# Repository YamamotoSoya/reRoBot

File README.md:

# reRoBot
Autonomous navigation robot for the Tsukuba Challenge

## Documentation
- **[docs/TODO.md](docs/TODO.md)** — 今取り組むこと (ジャンル別)
- **[docs/README.md](docs/README.md)** — docs/ 全体の地図 (調査記録・設計文書・解説書・月別変更履歴の索引)
- **[運用手引き (詳細版 README)](docs/manual/00_index.md)** — 全体像・セットアップ・基本パラメータ・起動と手動操作・bag 記録・SLAM (slam_toolbox / GLIM / LIO-SAM)・2D 地図変換・Nav2 / amcl・つくチャレ当日手順・トラブルシューティング・[ソフトウェア構成図](docs/manual/16_software_architecture.md)
- [CLAUDE.md](CLAUDE.md) — 開発規約・ビルド規則・アーキテクチャ要約
- [docs/text/](docs/text/README.md) — テーマ別解説書
- [docs/monthly/](docs/monthly/00_index.md) — 月別の変更履歴 (何を・なぜ変えたか、2026-03〜)

## Setup
### clone
Please add '--recursive' option when you clone this repository
```bash
$ git clone --recursive https://github.com/YamamotoSoya/reRoBot.git
```

If submodules are missing (cloned without `--recursive`):
```bash
$ git submodule update --init --recursive
```
### docker
```bash
$ xhost +local:docker          # set host before activate docker
$ ./scripts/build.sh images    # build images one by one (never `docker compose build` with no args)
$ docker compose up -d main    # activate (main only; other profiles when needed)
$ docker exec -it rerobot_env bash # enter
$ docker compose down          # deactivate
```
### colcon build
```bash
$ cd /workspace
$ rosdep update
$ rosdep install --from-paths src --ignore-src --simulate # check dependencies

$ colcon build --symlink-install --executor sequential
$ source install/setup.bash
```
### Hardware setup
* **USB-CAN アダプタ (CANUSB) — can0 は挿すだけで自動起動**

セットアップ済みのマシンでは、USB-CAN アダプタ (FTDI FT232, `0403:6001`) を挿すと
udev ルール → `/dev/ttyCANUSB` 作成 → systemd サービス `canusb-up.service` → `slcand` (1 Mbps) + `can0` up
まで全自動で行われる。**手動操作は不要**。状態確認・復旧は `./scripts/can_up.sh`。

```bash
$ ip link show can0        # 動作確認 (UP になっていれば OK)
$ ./scripts/can_up.sh      # 落ちているときの確認 + 復旧
```

<details>
<summary><b>新しいマシンをセットアップする手順 (初回のみ)</b></summary>

1. can-utils のインストール
```bash
$ sudo apt-get update && sudo apt-get install can-utils
```

2. カーネルモジュールの自動ロード設定 — `/etc/modules-load.d/can.conf` に以下を記述
```
can
can_raw
slcan
```

3. udev ルール — `/etc/udev/rules.d/99-hokuyo-devices.rules` (新規なら任意の `.rules` ファイル) に追記。
アダプタに固定名 `/dev/ttyCANUSB` を与え、挿入時に systemd サービスを起動させる
```
# CANUSB
SUBSYSTEM=="tty", ATTRS{idVendor}=="0403", ATTRS{idProduct}=="6001", SYMLINK+="ttyCANUSB", MODE="0666", TAG+="systemd", ENV{SYSTEMD_WANTS}="canusb-up.service"
```

4. systemd サービス — `/etc/systemd/system/canusb-up.service` を作成
```ini
[Unit]
Description=Setup CANUSB interface (can0)
After=dev-ttyCANUSB.device
BindsTo=dev-ttyCANUSB.device

[Service]
Type=oneshot
RemainAfterExit=yes
# 2026-09-19: USB 再列挙直後に自動起動した slcand が「can0 UP・送信可・受信ゼロ」の半死状態を
# 作ることがある (同日 3 回: 15:35, 17:16, 17:59。手動 restart で毎回復帰)。sleep 2 を入れても
# 17:59 に再発したので、待ち時間ではなく「起動後に受信を確認し、無ければ slcand をやり直す」で対処する。
ExecStartPre=/bin/sleep 2
ExecStart=/bin/bash -c 'slcand -o -c -s8 /dev/ttyCANUSB can0 && ip link set can0 up'
# EPOS のロジック電源が入っていれば heartbeat (2 ノード × 0.5 Hz) が 4 s 以内に届く。届かなければ 1 回やり直す。
ExecStartPost=/bin/bash -c 'sleep 4; [ "$(cat /sys/class/net/can0/statistics/rx_packets)" -gt 0 ] || { killall slcand; sleep 1; slcand -o -c -s8 /dev/ttyCANUSB can0 && ip link set can0 up; }'
ExecStop=/bin/bash -c 'ip link set can0 down; killall slcand'

[Install]
WantedBy=dev-ttyCANUSB.device
```

既にセットアップ済みのマシンで行を足すときは、上のファイルを編集してから
`sudo systemctl daemon-reload` (アダプタの挿し直しで反映)。半死状態の検知と復旧は
`./scripts/can_up.sh` でも行える (3 s 間 送信ありで受信ゼロなら service を再起動する)。
⚠️ 再列挙のたびに can0 は作り直され、稼働中の ros2_canopen master は旧 can0 を掴んだままになる
(`epos4_controller` が「can0 が作り直された … 再 launch が必要」を ERROR で出す) → `scripts/stop.sh` → 再 launch。

5. 有効化と動作確認
```bash
$ sudo systemctl daemon-reload
$ sudo systemctl enable canusb-up.service
$ sudo udevadm control --reload
# アダプタを挿し直して:
$ ip link show can0
```

※ `slcand -s8` が 1 Mbps 指定。can0 は slcan インターフェースなので、ビットレートを
`ip link set ... type can bitrate ...` で変更することはできない (slcand 側で決まる)。
</details>

* **3D LiDAR (R-Fans-16, Ethernet) — 挿すだけで自動接続**

セットアップ済みのマシンでは、LiDAR 用 USB-Ethernet アダプタ (`enx6c1ff7be7a78`) を挿すと
NetworkManager プロファイル `rfans` が自動適用され、ホストに静的 IP `192.168.0.100/24` が付く。
LiDAR 実機は `192.168.0.3` で、データは UDP 2014 へブロードキャストされる (ホスト側 IP を LiDAR に教える必要はない)。
コンテナは `network_mode: host` なので、ホストに IP が付けば追加設定なしで届く。

```bash
$ ip -br addr show enx6c1ff7be7a78   # 192.168.0.100/24 が付いていれば OK
$ ping -c 3 192.168.0.3              # LiDAR 疎通確認
```

<details>
<summary><b>新しいマシン / 別のアダプタをセットアップする手順 (初回のみ)</b></summary>

NetworkManager に「このアダプタが現れたら固定 IP を付ける」プロファイルを 1 度作るだけ。
`ip addr add` と違い再起動・抜き差しをまたいで自動適用される。

1. LiDAR 用アダプタを挿し、インターフェース名を確認 (`enx` + アダプタの MAC。個体固有で、
   どの USB ポート/ハブ経由でも同じ名前になる)

```bash
$ ip -br link      # 例: enxcce1d5021885
```

2. プロファイル作成 (`ifname` は上で確認した名前に差し替える)

```bash
$ nmcli connection add type ethernet \
    con-name rfans \
    ifname enxcce1d5021885 \
    ipv4.method manual \
    ipv4.addresses 192.168.0.100/24 \
    connection.autoconnect yes \
    connection.autoconnect-priority 100
$ nmcli connection up rfans   # 初回のみ即時有効化 (以後は挿すだけで自動)
```

3. 疎通確認

```bash
$ ip -br addr show <ifname>   # 192.168.0.100/24 が付いていること
$ ping -c 3 192.168.0.3
```

※ gateway を指定していないのでデフォルトルートは奪わず、Wi-Fi のインターネット接続と共存できる。
※ `ifname` 紐付けは MAC 由来名なので「この個体 = LiDAR 係」の専用化が前提。アダプタを
別個体に交換したら手順 1〜2 をやり直す (`nmcli con delete rfans` で旧設定を消してから)。
※ `autoconnect-priority 100` は、ifname 指定なしの汎用「Wired connection」系プロファイルとの
競合時に rfans を勝たせるための指定。
</details>

* **2D LiDAR (HOKUYO UTM-30LX) — 挿すだけで固定名 `/dev/ttyUSB-utm-30lx`**

udev ルールにより、挿すと固定名 `/dev/ttyUSB-utm-30lx` (権限 0666) が作られる。
この名前は `rerobot_bringup_2d.launch.py` の `serial_port` デフォルト値と一致しているので、
**挿すだけで 2D bringup がそのまま動く** (systemd サービス等は不要 — シリアル直結なので
名前と権限さえ固定できればよい)。

```bash
$ ls -l /dev/ttyUSB-utm-30lx    # symlink が ttyUSB* を指していれば OK
```

<details>
<summary><b>新しいマシンをセットアップする手順 (初回のみ)</b></summary>

CANUSB と同じ `/etc/udev/rules.d/99-hokuyo-devices.rules` に追記:

```
# UTM-30LX
SUBSYSTEM=="tty", ATTRS{idVendor}=="15d1", ATTRS{idProduct}=="0000", SYMLINK+="ttyUSB-utm-30lx", MODE="0666"
```

```bash
$ sudo udevadm control --reload
# 挿し直して:
$ ls -l /dev/ttyUSB-utm-30lx
```

※ `MODE="0666"` は「dialout グループに入っていなくても読み書きできる」ようにするため。
これが無いと urg_node が Permission denied で落ちる。
</details>

* **IMU (BNO086 ボード) — 挿すだけで固定名 `/dev/bno086`**

udev ルールにより、通常動作 (firmware 書き込み済み) のボードを挿すと固定名 `/dev/bno086`
(権限 0666) が作られる。番号が変動する `/dev/ttyACM*` を追いかける必要はない。
`bno086_imu_driver` の `port` パラメータ既定値は `/dev/ttyACM0` なので、起動時は
`port:=/dev/bno086` を指定する。

```bash
$ ls -l /dev/bno086             # symlink が ttyACM* を指していれば OK
```

<details>
<summary><b>新しいマシンをセットアップする手順 (初回のみ)</b></summary>

ルールはドライバ同梱の `ros2_ws_main/src/drivers/BNO086_ROS2Board-main/tools/99-bno086.rules`
と同内容。`/etc/udev/rules.d/99-hokuyo-devices.rules` に追記でも、同梱ファイルの
`sudo cp` でもよい:

```
# bno086
# Running firmware: USB CDC. Note that 0483:5740 is ST's generic CDC pair, so
# any other STM32 CDC device would match too - drop the SYMLINK line if you
# have more than one plugged in at once.
SUBSYSTEM=="tty", ATTRS{idVendor}=="0483", ATTRS{idProduct}=="5740", MODE="0666", SYMLINK+="bno086"

# ROM bootloader (S2 BOOT + S1 RESET), so STM32_Programmer_CLI / dfu-util can
# flash without sudo.
SUBSYSTEM=="usb", ATTRS{idVendor}=="0483", ATTRS{idProduct}=="df11", MODE="0666"

# ST-Link, for SWD flashing via OpenOCD / st-flash.
SUBSYSTEM=="usb", ATTRS{idVendor}=="0483", ATTRS{idProduct}=="374b", MODE="0666"
SUBSYSTEM=="usb", ATTRS{idVendor}=="0483", ATTRS{idProduct}=="3748", MODE="0666"
```

```bash
$ sudo udevadm control --reload
# 挿し直して:
$ ls -l /dev/bno086
```

3 ブロックの役割:

| ブロック | ボードの状態 | 用途 |
|----------|--------------|------|
| `0483:5740` (CDC) | 通常動作 (firmware 実行中) | IMU データ読み取り。`/dev/bno086` を作る |
| `0483:df11` (DFU) | ROM ブートローダ (S2 BOOT + S1 RESET で起動) | `STM32_Programmer_CLI` / `dfu-util` での firmware 書き込みを sudo なしで |
| `0483:374b` / `3748` (ST-Link) | — (書き込み器側) | OpenOCD / st-flash での SWD 書き込みを sudo なしで |

※ `0483:5740` は ST 汎用の CDC ID なので、**別の STM32 CDC デバイスを同時に挿すと
そちらにも `/dev/bno086` が付き得る**。複数挿す運用になったら SYMLINK 行を外すか
シリアル番号 (`ATTRS{serial}`) で絞る。
</details>

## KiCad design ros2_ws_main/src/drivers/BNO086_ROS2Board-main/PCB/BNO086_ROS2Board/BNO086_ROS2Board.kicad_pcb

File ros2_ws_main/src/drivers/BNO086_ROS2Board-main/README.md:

# BNO086_ROS2Board

BNO086 (9軸IMU) + STM32F042 の自作基板を、ROS 2 の IMU センサとして使うための
一式です。回路図・基板データからファームウェア、ROS 2 パッケージまで全部入りです。

```
┌──────────────┐   SPI    ┌──────────────┐   USB CDC / UART   ┌─────────────┐
│   BNO086     ├─────────►│  STM32F042C6 ├───────────────────►│   ROS 2     │
│  (SH-2/SHTP) │          │  (firmware/) │   独自バイナリ      │  (ros2_ws/) │
└──────────────┘          └──────────────┘                    └─────────────┘
                                                    sensor_msgs/Imu
                                                    sensor_msgs/MagneticField
```

| ディレクトリ | 内容 |
|---|---|
| `PCB/` | KiCad の回路図・基板データ (既存) |
| `firmware/` | STM32F042C6 用ファームウェア (CMake + STM32 HAL) |
| `ros2_ws/` | ROS 2 ワークスペース (`bno086_imu_driver` パッケージ) |
| `tools/` | udev ルール、シリアル↔TCP 中継 |
| `docker/` | ROS 2 コンテナ (macOS 用。[付録](#付録-macos-で動かす)) |
| `docs/` | [ハードウェア仕様](docs/HARDWARE.md) / [プロトコル仕様](docs/PROTOCOL.md) |

## 動作環境

**Ubuntu 24.04 + ROS 2 Jazzy をネイティブに入れた PC** を前提にしています。
基板は USB CDC で `/dev/ttyACM*` として見えるので、追加のハードウェアは要りません。

| | 用途 | 備考 |
|---|---|---|
| **ROS 2 Jazzy** | ドライバの実行 | 他のディストリでも動くはずですが未検証 |
| **python3-serial** | シリアル通信 | `rosdep` で入ります |
| **ARM ツールチェーン** | ファームウェアのビルド | 書き込み済みの基板を使うだけなら不要 |
| **書き込み手段** | 基板への書き込み | USB だけで済む DFU、または ST-Link |

macOS でも動きますが、Docker Desktop が USB を渡せないため中継が要ります。
開発中の検証用なので[付録](#付録-macos-で動かす)にまわしました。

## クイックスタート

書き込み済みの基板と ROS 2 Jazzy が手元にある場合。

```bash
git clone https://github.com/MechanicalGirlDev/BNO086_ROS2Board.git
cd BNO086_ROS2Board

# シリアルポートの権限 (これを忘れると Permission denied になります)
sudo cp tools/99-bno086.rules /etc/udev/rules.d/
sudo udevadm control --reload-rules && sudo udevadm trigger

source /opt/ros/jazzy/setup.bash
cd ros2_ws
rosdep install --from-paths src --ignore-src -r -y
colcon build --symlink-install && source install/setup.bash

ros2 launch bno086_imu_driver bno086.launch.py port:=/dev/bno086
```

`ros2 topic hz /imu/data` で 100 Hz 出ていれば成功です。
ROS 2 をまだ入れていない場合は [3. PC 側 ROS 2 環境](#3-pc-側-ros-2-環境) から。

| 手順 | 節 |
|---|---|
| ファームウェアをビルドする | [1](#1-ファームウェアのビルド) |
| 基板に書き込む | [2](#2-書き込み) |
| ROS 2 とこのパッケージを入れる | [3](#3-pc-側-ros-2-環境) |
| ノードを起動してトピックを見る | [4](#4-実行) |
| 座標系と実装角度を理解する | [座標系](#座標系) |
| キャリブレーションする | [5](#5-キャリブレーション) |
| うまくいかないとき | [トラブルシューティング](#トラブルシューティング) |
| 既知の問題を確認する | [実機での検証状況](#実機での検証状況) |
| macOS で動かす (検証用) | [付録](#付録-macos-で動かす) |

## 設計方針

**micro-ROS は使っていません。** STM32F042C6 は RAM 6 KiB / Flash 32 KiB しかなく、
micro-ROS (最低でも RAM 30 KiB 程度) は載りません。代わりに軽量な独自バイナリ
プロトコルで PC に送り、PC 側の ROS 2 ノードが `sensor_msgs/Imu` に変換します。

同じ理由で、CEVA 公式の `sh2` ライブラリではなく、必要な部分だけを実装した
軽量 SHTP/SH-2 クライアント (`firmware/App/bno08x.c`) を使っています。
MCU 側は浮動小数点演算を一切行わず、BNO086 の固定小数点値をそのまま転送します。

現在の使用量: **Flash 19.5 KiB / 32 KiB (61%)、RAM 4.6 KiB / 6 KiB (78%)**

---

## 1. ファームウェアのビルド

書き込み済みの基板を使うだけならこの節は飛ばせます。

```bash
sudo apt install gcc-arm-none-eabi binutils-arm-none-eabi \
                 libnewlib-arm-none-eabi cmake ninja-build

cmake -S firmware -B build/fw -G Ninja
cmake --build build/fw
```

`build/fw/bno086_ros2board.{elf,bin,hex}` ができます。
依存する ST のライブラリ (HAL / CMSIS / USB Device) は CMake の FetchContent が
自動取得するので、初回ビルドのみネットワークが必要です。

ツールチェーンをホストに入れたくない場合は Docker でも同じことができます。

```bash
docker build -t bno086-fw firmware/
docker run --rm -v "$PWD":/work -w /work bno086-fw bash -c \
  'cmake -S firmware -B build/fw -G Ninja && cmake --build build/fw'
```

### 出力先の切り替え

USB と UART は排他です (どちらか一方が詰まってもう一方が止まる事故を防ぐため)。

```bash
# USB CDC (デフォルト)
cmake -S firmware -B build/fw -G Ninja

# USART1 (J4) に出す場合
cmake -S firmware -B build/fw-uart -G Ninja -DHOST_LINK_USB=OFF -DHOST_LINK_UART=ON
```

UART のボーレートは `-DUART_BAUD=921600` で変更できます。

## 2. 書き込み

J3 (SWD) に ST-Link を接続してください。

```bash
# OpenOCD
openocd -f interface/stlink.cfg -f target/stm32f0x.cfg \
        -c "program build/fw/bno086_ros2board.elf verify reset exit"

# あるいは st-flash
st-flash write build/fw/bno086_ros2board.bin 0x08000000
```

### USB DFU で書き込む (ST-Link 不要)

STM32F042 は DFU ブートローダを内蔵しているので、USB ケーブルだけで書き込めます。
**S2 (BOOT) を押しながら S1 (RESET) を押して離す** と DFU モードに入ります
(`lsusb` に `0483:df11` が出ます)。

```bash
sudo apt install dfu-util
dfu-util -a 0 -s 0x08000000:leave -D build/fw/bno086_ros2board.bin
```

書き込みのたびにこのボタン操作が必要です。udev ルール
(`tools/99-bno086.rules`) を入れておくと `sudo` なしで書き込めます。

macOS で STM32CubeProgrammer を使う場合 (実機での書き込みはこの経路で確認済み):

```bash
CLI=/Applications/STM32CubeIDE.app/Contents/Eclipse/plugins/\
com.st.stm32cube.ide.mcu.externaltools.cubeprogrammer.macos64_*/tools/bin/STM32_Programmer_CLI
$CLI -c port=usb1 -w build/fw/bno086_ros2board.hex -v -g
```

### 書き込み前の確認

**JP1 / JP2 はどちらもオープンのまま** にしてください。
BNO086 の SPI モードは **PS1=1 / PS0=1** で選択されます。PS1 は R7 のプルアップ、
PS0 はファームウェアが PB0 を High に保つことで実現します (両方が NRST 解除前から
High である必要があります)。JP1 を短絡すると PB0 が GND と衝突します。
詳細は [docs/HARDWARE.md](docs/HARDWARE.md)。

### LED の意味

| LED | 状態 | 意味 |
|---|---|---|
| LED1 (PB12) | 1 Hz 点滅 | 正常動作中 |
| LED2 (PB13) | 点灯 | BNO086 と通信できている |
| 両方 | 高速点滅 | 致命的エラー (`board_error()`) |

## 3. PC 側 ROS 2 環境

### ROS 2 Jazzy を入れる (Ubuntu 24.04)

すでに入っている場合は次の「[このパッケージをビルドする](#このパッケージをビルドする)」へ。

```bash
sudo apt install software-properties-common curl
sudo add-apt-repository universe
sudo curl -sSL https://raw.githubusercontent.com/ros/rosdistro/master/ros.key \
     -o /usr/share/keyrings/ros-archive-keyring.gpg
echo "deb [arch=$(dpkg --print-architecture) signed-by=/usr/share/keyrings/ros-archive-keyring.gpg] \
http://packages.ros.org/ros2/ubuntu $(. /etc/os-release && echo $UBUNTU_CODENAME) main" \
  | sudo tee /etc/apt/sources.list.d/ros2.list > /dev/null

sudo apt update
sudo apt install ros-jazzy-ros-base python3-colcon-common-extensions python3-rosdep
```

(公式手順は [ROS 2 Jazzy のインストール](https://docs.ros.org/en/jazzy/Installation/Ubuntu-Install-Debs.html)
を参照してください。上記はその要約です。)

### このパッケージをビルドする

```bash
source /opt/ros/jazzy/setup.bash

# 依存 (rclpy, sensor_msgs, tf2_ros, python3-serial ...) をまとめて入れる
sudo rosdep init      # 初回のみ
rosdep update
cd ros2_ws && rosdep install --from-paths src --ignore-src -r -y

colcon build --symlink-install
source install/setup.bash
```

`~/.bashrc` に次を足しておくと毎回の source が要らなくなります。

```bash
echo "source /opt/ros/jazzy/setup.bash" >> ~/.bashrc
echo "source $PWD/install/setup.bash"   >> ~/.bashrc
```

`--symlink-install` を付けているので、Python を書き換えたときの再ビルドは
不要です (`launch` / `config` を追加したときだけ `colcon build` し直します)。

### シリアルポートの権限

素の状態では `/dev/ttyACM0` を開けず `Permission denied` になります。
同梱の udev ルールを入れてください。

```bash
sudo cp tools/99-bno086.rules /etc/udev/rules.d/
sudo udevadm control --reload-rules && sudo udevadm trigger
```

USB に挿し直すと **`/dev/bno086`** ができます。ポート番号に依存しない名前なので、
他の USB シリアル機器を抜き挿ししても変わりません。launch では
`port:=/dev/bno086` と書いてください。

udev を使わない場合は `sudo usermod -aG dialout $USER` でも通ります
(**再ログインが必要**)。

## 4. 実行

```bash
ros2 launch bno086_imu_driver bno086.launch.py port:=/dev/bno086
```

publish されるトピック:

| トピック | 型 |
|---|---|
| `/imu/data` | `sensor_msgs/Imu` |
| `/imu/mag` | `sensor_msgs/MagneticField` |
| `/diagnostics` | `diagnostic_msgs/DiagnosticArray` |

確認:

```bash
ros2 topic hz /imu/data
ros2 topic echo /imu/data --once
```

## 座標系

publish されるデータは **基板の座標系** (`frame_id: imu_link`) です。
右手系で、Z が基板の部品面側 (上) を向きます。X / Y は基板レイアウトの
X / Y 軸に一致します。

姿勢クォータニオンは **body → world** (基板座標系から重力・地磁気基準の世界座標系へ)
の変換です。実機で確認済み (誤差 0.128 / 逆向き解釈だと 1.247)。

> **重要:** BNO086 (U4) はこの基板上で **180° 回転して実装** されています
> (KiCad 上で `回転=180°`)。そのためチップの +X / +Y は基板の −X / −Y を向きます
> (+Z は一致)。ROS 2 ノードは `mount_yaw_deg: 180.0` でこれを補正してから
> publish するので、**利用側で符号を反転する必要はありません**。
> センサの生の座標系がほしい場合は `mount_yaw_deg: 0.0` にしてください。
> 詳細は [docs/HARDWARE.md](docs/HARDWARE.md) の「実装角度」。

機体に対する取り付け向き (前後・左右) は、このパラメータではなく
ロボット側の static transform (`imu_link` → `base_link`) で表現してください。
[REP-103](https://www.ros.org/reps/rep-0103.html) / [REP-145](https://www.ros.org/reps/rep-0145.html)
に沿った運用です。

### 主なパラメータ

`ros2_ws/src/bno086_imu_driver/config/bno086.yaml` を参照。

| パラメータ | 既定値 | 内容 |
|---|---|---|
| `port` | `/dev/ttyACM0` | シリアルデバイス。udev ルールを入れたら `/dev/bno086` |
| `frame_id` | `imu_link` | メッセージの frame_id |
| `imu_rate_hz` | `100.0` | IMU の報告レート (最大400程度) |
| `mag_rate_hz` | `25.0` | 地磁気の報告レート |
| `use_device_time` | `true` | 基板側クロックでタイムスタンプする |
| `publish_tf` | `false` | 姿勢を TF として配信する |
| `mount_yaw_deg` | `180.0` | U4 の実装角度の補正 ([座標系](#座標系)) |
| `auto_tare` | `all` | 起動・リセット時の自動原点合わせ (`off` / `yaw` / `all`) |
| `auto_tare_delay` | `2.0` | 自動 tare までの待ち時間 [s] |
| `use_game_rotation_vector` | `false` | 地磁気を使わない Game RV に切り替える |
| `angular_velocity_stddev` | `0.005` | 共分散に使う標準偏差 [rad/s] |
| `linear_acceleration_stddev` | `0.05` | 同 [m/s²] |

### 自動原点合わせ (auto_tare)

`auto_tare` を設定しておくと、**ストリームが立ち上がるたび**(ノード起動、S1 での
基板リセット、`reset` サービス) に、そのときの姿勢を原点にします。既定は `all` です。

| 値 | 動作 |
|---|---|
| `off` | センサ本来の基準のまま publish する |
| `yaw` | 方位だけゼロにする。roll / pitch は重力基準のまま |
| `all` | 3軸すべてゼロにして (0, 0, 0) から始める |

融合が落ち着くまで `auto_tare_delay` 秒待ってから実行します。

> YAML では `off` が真偽値に解釈されるため、コマンドラインでは
> `-p auto_tare:=off` のように文字列として渡しても動くようにしてあります。
> `use_game_rotation_vector: true` のときは tare が効かないため機能しません。

### 自動再接続

S1 (RESET) を押すと MCU が再起動して USB CDC が一度切れますが、ノードは
1 秒ごとに再接続を試み、復帰したらレート設定を送り直します。基板側の
マイクロ秒カウンタも 0 に戻るため、時刻推定もリセットしています。

```
[ERROR] serial error: read failed: socket disconnected
[INFO]  reconnected
[INFO]  requested 100 Hz IMU / 25 Hz magnetometer
```

実測で **約4秒で復帰** します (TCP 中継を挟んだ場合。中継側も基板が USB から
消えている間は待機して再オープンします)。

### サービス

**`tare` と `reset` は別物です。** 姿勢をゼロにしたいときは `tare` を使ってください。
`reset` は BNO086 を再起動するだけで、tare は解除され地磁気基準の方位に戻ります
(S1 ボタンも同じです)。

```bash
# 方位(yaw)だけをゼロにする ← ロボット用途はたいていこちら
# roll/pitch は重力基準のまま残ります
ros2 service call /bno086_imu_driver/tare_yaw std_srvs/srv/Trigger

# 3軸すべてをゼロにする
ros2 service call /bno086_imu_driver/tare std_srvs/srv/Trigger

# 動的キャリブレーション結果を保存
ros2 service call /bno086_imu_driver/save_calibration std_srvs/srv/Trigger

# BNO086 を再起動 (tare は解除される)
ros2 service call /bno086_imu_driver/reset std_srvs/srv/Trigger
```

### RViz2 で見る

Ubuntu ネイティブなら RViz2 がそのまま使えます。

```bash
sudo apt install ros-jazzy-rviz2 ros-jazzy-imu-tools

# 姿勢を TF として出す
ros2 launch bno086_imu_driver bno086.launch.py port:=/dev/bno086 \
  --ros-args -p publish_tf:=true

ros2 run rviz2 rviz2
```

Fixed Frame を `odom` にして TF を追加するか、`imu_tools` の
`rviz_imu_plugin` で `/imu/data` を直接表示できます。

### ブラウザで可視化

RViz2 を入れずに済ませたいとき用に、ブラウザで見られる可視化ノードもあります
(元は X サーバのない環境向けに書いたものです)。ROS 2 のトピックを購読して
いるので、「ROS 2 で動いていること」がそのまま確認できます。

```bash
ros2 run bno086_imu_driver imu_viz
# visualiser on http://localhost:8080
```

ブラウザで <http://localhost:8080> を開くと、姿勢の 3D 表示、roll/pitch/yaw、
角速度・加速度・地磁気の生値、受信数、診断メッセージが 30 fps で更新されます。

### ROS 抜きでの動作確認

基板の立ち上げ時はこちらが便利です。

```bash
ros2 run bno086_imu_driver serial_monitor --port /dev/bno086
# 100 Hz imu /  25 Hz mag  rpy=(  +0.31,  -1.02, +45.77)deg  acc=3 resets=0 ...

# 全フレームをダンプ
ros2 run bno086_imu_driver serial_monitor --port /dev/bno086 --raw
```

## 5. キャリブレーション

BNO086 は動的キャリブレーションを行うので、初回は基板を各軸まわりに
ゆっくり回してください。`/diagnostics` の `orientation_accuracy` が
`high` になったら `save_calibration` サービスで保存します。

`/diagnostics` が `unreliable` のままの場合、地磁気が乱れた場所
(モータやスチール机の近く) が原因のことが多いです。

## トラブルシューティング

まず [`serial_monitor`](#ros-抜きでの動作確認) を実行してください。ROS を挟まずに
基板と直接話すので、問題が基板側かホスト側かを切り分けられます。

| 症状 | 原因と対処 |
|---|---|
| ポートが見つからない | `ls /dev/ttyACM*` で確認。何も出なければ USB ケーブルが充電専用の可能性があります (データ線のあるものを使う)。`dmesg \| tail` に `cdc_acm` が出ているかも見てください |
| `/dev/bno086` ができない | udev ルールを入れたあと、**USB を挿し直す**必要があります。`udevadm info -a -n /dev/ttyACM0 \| grep idVendor` が `0483` かも確認 |
| `Permission denied` | udev ルールを入れる ([シリアルポートの権限](#シリアルポートの権限))。`dialout` グループに入れた場合は再ログインが必要 |
| LED1 が点滅しない | ファームウェアが動いていません。書き込みからやり直してください |
| LED1 は点滅するが LED2 が消灯 | BNO086 と通信できていません。**JP1 / JP2 がオープンか**を確認 (SPI 選択には PS1=1 / PS0=1 が必要)。`serial_monitor` が到達段階と SPI モード自動走査の結果を表示します |
| トピックが出ない / `topic hz` が無反応 | `ros2 node list` にノードがいるか確認。いるのにデータが来ない場合はログの `serial error` を確認 |
| `rosdep: command not found` | `sudo apt install python3-rosdep`、`sudo rosdep init`、`rosdep update` |
| `ModuleNotFoundError: serial` | `sudo apt install python3-serial` |
| `ModuleNotFoundError: bno086_imu_driver` | `source install/setup.bash` を忘れています。テストを直接動かす場合は `ros2_ws/src/bno086_imu_driver` に移動してから実行してください |
| yaw がリセットで 0 に戻らない | 仕様です ([理由](#yaw-がリセットで-0-に戻らない理由))。`auto_tare` か `tare_yaw` を使ってください |
| 姿勢が実機と逆に動く | `mount_yaw_deg` が `0.0` になっていないか確認 ([座標系](#座標系)) |
| `/diagnostics` が `unreliable` のまま | 地磁気の乱れです。場所を変えるか `use_game_rotation_vector: true` |
| 100 Hz より遅い / 取りこぼす | 200 Hz 超は SHTP が飽和します ([実測レート](#実測レート)) |

## テスト

**52件、実機不要**です。擬似端末 (pty) を使って、フレーム生成 → pyserial →
パーサ → ROS メッセージまでを通しで検証しています。

```bash
source /opt/ros/jazzy/setup.bash
cd ros2_ws/src/bno086_imu_driver && python3 -m pytest test -q
```

push / PR ごとに [GitHub Actions](.github/workflows/ci.yml) が、
ファームウェアのビルド (USB / UART の両構成) とこのテストを実行します。

## 実機での検証状況

> **検証はすべて macOS + Docker + TCP 中継の環境で行いました。**
> ROS 2 の層より下 (ファームウェア、SPI/SHTP、フレーム、レート、tare) は
> 環境に依存しないのでそのまま通用しますが、**Ubuntu ネイティブでの実機確認は
> まだです**。udev ルールと `/dev/ttyACM0` 直結の部分は初回に確認してください。

### 動作確認済み (実機)

| 項目 | 結果 |
|---|---|
| USB CDC 列挙 | `/dev/cu.usbmodem*` として認識。48 MHz クロック正常 |
| DFU 書き込み | STM32CubeProgrammer でベリファイまで成功 |
| BNO086 SPI 通信 | 段階4 (reset complete)、リセット試行1回で確立 |
| クォータニオン | \|q\| = 1.0000 |
| 加速度 | \|a\| = 9.6 m/s² (重力と一致) |
| 地磁気 | 25 Hz で受信 |
| 通信品質 | 長時間受信で CRC エラー 0 / 再同期 0 |
| レート制御 | `SET_RATE` が反映される |
| ROS 2 ノード | macOS の Docker + TCP 中継で `/imu/data` を 100.2 Hz で publish |
| tare (3軸) | 0.3 秒で姿勢が (0,0,0) になることを確認 |
| tare (yawのみ) | yaw だけゼロ化、roll/pitch の変化 0.03° |
| 姿勢の安定性 | 静置 45 秒でドリフト −0.45 °/分、精度 high |
| 地磁気 | 静置時 \|B\| = 38.1 µT (地磁気の正常範囲) |
| 自動再接続 | 切断から約 4 秒で復帰 |
| 自動 tare | S1 リセット後、再接続して自動で (0,0,0) に復帰 |
| 実装角度の補正 | `mount_yaw_deg: 180.0` 適用後、加速度 \|a\| = 9.62 m/s² / 100.1 Hz |
| クォータニオンの向き | body → world であることを確認 (誤差 0.128 / 逆向き 1.247) |
| 可視化 | ブラウザ表示が実機の回転と一致 |

### 実測レート

`SET_RATE` を変えながら、姿勢・角速度・加速度が 1 フレームに揃っている割合を
測定した結果です。

| 要求レート | 実測 | 全項目揃い |
|---|---|---|
| 100 Hz | 100 Hz | **100 %** |
| 200 Hz | 192 Hz | **99.7 %** |
| 250 Hz | 150 Hz | 92.9 % |
| 400 Hz | 189 Hz | 46 % |

**実用上の上限は 200 Hz 程度** です。既定値の 100 Hz なら常に全項目が揃います
(ロボティクス用途では 100 Hz あれば十分なことがほとんどです)。

200 Hz を超えると SHTP パケットの取得が **約 800 パケット/秒で飽和** します。
地磁気を無効にしても変わらないため、BNO086 のセンサ帯域ではなくファームウェア側
の取得経路 (1 ループ 1 パケット、CS ごとのオーバーヘッド、`board_micros()` の
ソフトウェア除算) が律速していると考えられます。**根本原因は未特定** です。
400 Hz が必要な場合は、1 ループで複数パケットを読む、SysTick 由来の除算を除く、
といった最適化が要ります。

### 立ち上げで踏んだ問題 (すべて解決済み)

1. **PS0 ストラップの誤り** — SPI 選択は `PS1=1, PS0=1` で、**両方が NRST 解除前から
   最初の H_INTN アサートまで High** である必要があります (データシート 1.2.4 /
   Figure 1-20)。当初 PS0 を Low にしていたため UART-RVC で起動し、SPI に一切
   応答しませんでした。
2. **SPI 待ちループのタイムアウト欠如** — SPI が応答しないとメインループが停止し、
   USB は列挙されたままデータだけ止まる状態になっていました。
3. **不正な SHTP ヘッダの受理** — `len=17792` のようなノイズを真に受けて大量に
   クロックを出していました。チャンネルと長さを検証するようにしました。

立ち上げ用の診断機能は残してあります。IMU が起動しない場合、`serial_monitor` が
到達段階・SPI モード自動走査 (4モード × 2クロック)・MISO/H_INTN のピンレベル判定を
表示します。

### yaw がリセットで 0 に戻らない理由

Rotation Vector は**地磁気で北を基準にした絶対方位**です。電源投入時からの相対角
ではないため、リセットしても同じ物理的方位を測り直すだけで 0 にはなりません。
0 にしたいときは `tare` / `tare_yaw` を使ってください。

`use_game_rotation_vector: true` にすると地磁気を使わない Game Rotation Vector に
切り替わります。磁気外乱に強い一方、**tare が効きません**(下記)。屋内静置での
実測では磁気RV/Game RV ともドリフトは 0.5 °/分以下、精度は high でした。
モーターや鉄骨で地磁気が乱れる環境でなければ、既定の磁気RV のままで問題ありません。

> 測定は基板を静置して行ってください。持ち運びながらの測定では地磁気が
> 数百 µT に振れ、姿勢精度も 0 のままになります。

### そのほか未検証

- **Save DCD (`0x06`)** — CEVA の SH-2 リファレンスに基づく実装で、実機応答は
  未確認です。
- **Game Rotation Vector では tare が効きません** — `use_game_rotation_vector: true`
  のとき、tare を送っても yaw が変化しません (実測 +172.12 → +172.14)。SH-2 の
  tare basis を Gaming Rotation Vector (1) に切り替えても改善しませんでした。
  原因は未特定です。tare が必要な場合は既定の磁気RV をお使いください。
- **tare の永続化が効きません** — `tare` / `tare_yaw` は姿勢を確実にゼロにしますが
  (実機確認済み)、「Persist Tare」(サブコマンド 1) が効いておらず、IMU をリセット
  すると tare が失われて地磁気基準の方位に戻ります。**起動のたびに tare し直す
  運用**でご利用ください。既定の `auto_tare: all` がこれを自動で行います。

  原因は未特定です。BNO086 は Tare コマンドに対して SH-2 コマンドレスポンスを
  返さないため (実機で 0 件)、受理されたか否かを応答から判定できませんでした。
  tare 本体は効いているので、コマンド自体は届いています。
- **CAN** — 回路はありますがファームウェアは未実装です。加えて U5 の `Vio` が
  +5 V に配線されている点は要確認です ([docs/HARDWARE.md](docs/HARDWARE.md))。

### 実装を見送ったもの

動作中のファームから ROM ブートローダへジャンプする `ENTER_DFU` コマンドを
試しましたが、この石では BOOT0 が Low だとブートローダがユーザーコードへ
戻ってしまい DFU として列挙しませんでした。削除済みです。書き込みのたびに
S2 (BOOT) + S1 (RESET) のボタン操作が必要です。

また `PCB/BNO086_ROS2Board.ioc` は基板と一致していません (割り込みが `PF11` に
なっている等)。本ファームウェアは CubeMX 生成に依存しないため実害はありませんが、
CubeMX を使う場合は先に修正してください。

## 付録: macOS で動かす

**開発中の検証に使った構成**です。常用するなら Ubuntu ネイティブをおすすめします。

macOS には ROS 2 をネイティブに入れられないのでコンテナを使いますが、
Docker Desktop for Mac は USB デバイスをコンテナに渡せません。そこで
**シリアルを TCP で中継** します。pyserial の `socket://` URL に対応済みなので、
ドライバ側は URL を渡すだけです。

ターミナル1 (macOS ホスト側):

```bash
pip3 install pyserial
ls /dev/cu.usbmodem*                  # 基板が見えているか確認

python3 tools/serial_bridge.py --port '/dev/cu.usbmodem*' --listen 5555
# [bridge] opened /dev/cu.usbmodem205B386A48581
# [bridge] listening on 0.0.0.0:5555
```

ターミナル2 (コンテナ内):

```bash
cd docker
docker compose build                  # 初回のみ。10分程度かかります
docker compose run --rm --service-ports ros2

colcon build --symlink-install && source install/setup.bash
ros2 launch bno086_imu_driver bno086.launch.py \
    port:=socket://host.docker.internal:5555
```

`--service-ports` はブラウザ可視化 (8080番) を使うときに必要です。
`ros2_ws/` はホストからマウントされているので、ホスト側のエディタでの編集が
そのまま反映されます。

これで `/imu/data` が 100 Hz で流れます (実機で確認済み)。

同じ仕組みで、**別マシンに挿した基板をネットワーク越しに読む**こともできます
(`--bind` と `socket://<ホスト>:5555`)。Ubuntu 機からノートPCに挿した基板を
読む、といった使い方ができます。

うまく繋がらないときは、中継が動いているか (`[bridge] listening on ...`)、
`--service-ports` を付けたか、`host.docker.internal` が引けるか
(`docker-compose.yml` の `extra_hosts`) を確認してください。

Linux ホストで同じコンテナを使う場合は中継は不要で、`docker-compose.yml` の
`devices:` を有効にして `port:=/dev/ttyACM0` を直接渡せます。

> ROS 2 を macOS にネイティブで入れたい場合は
> [RoboStack](https://robostack.github.io/) (conda-forge 版) が使えます。
> その場合は中継なしで `/dev/cu.usbmodem*` を直接指定できます。

## ライセンス

[MIT](LICENSE)。ただし `firmware/` がビルド時に取得する STMicroelectronics の
ライブラリはそれぞれのライセンス (Apache-2.0 / BSD-3-Clause 等) に従います。

PCB データ (`PCB/`) も同じ MIT で公開しています。基板を起こす場合は
[docs/HARDWARE.md](docs/HARDWARE.md) の既知の注意点 (U5 `Vio` の配線、`.ioc` の
不一致) を先に確認してください。

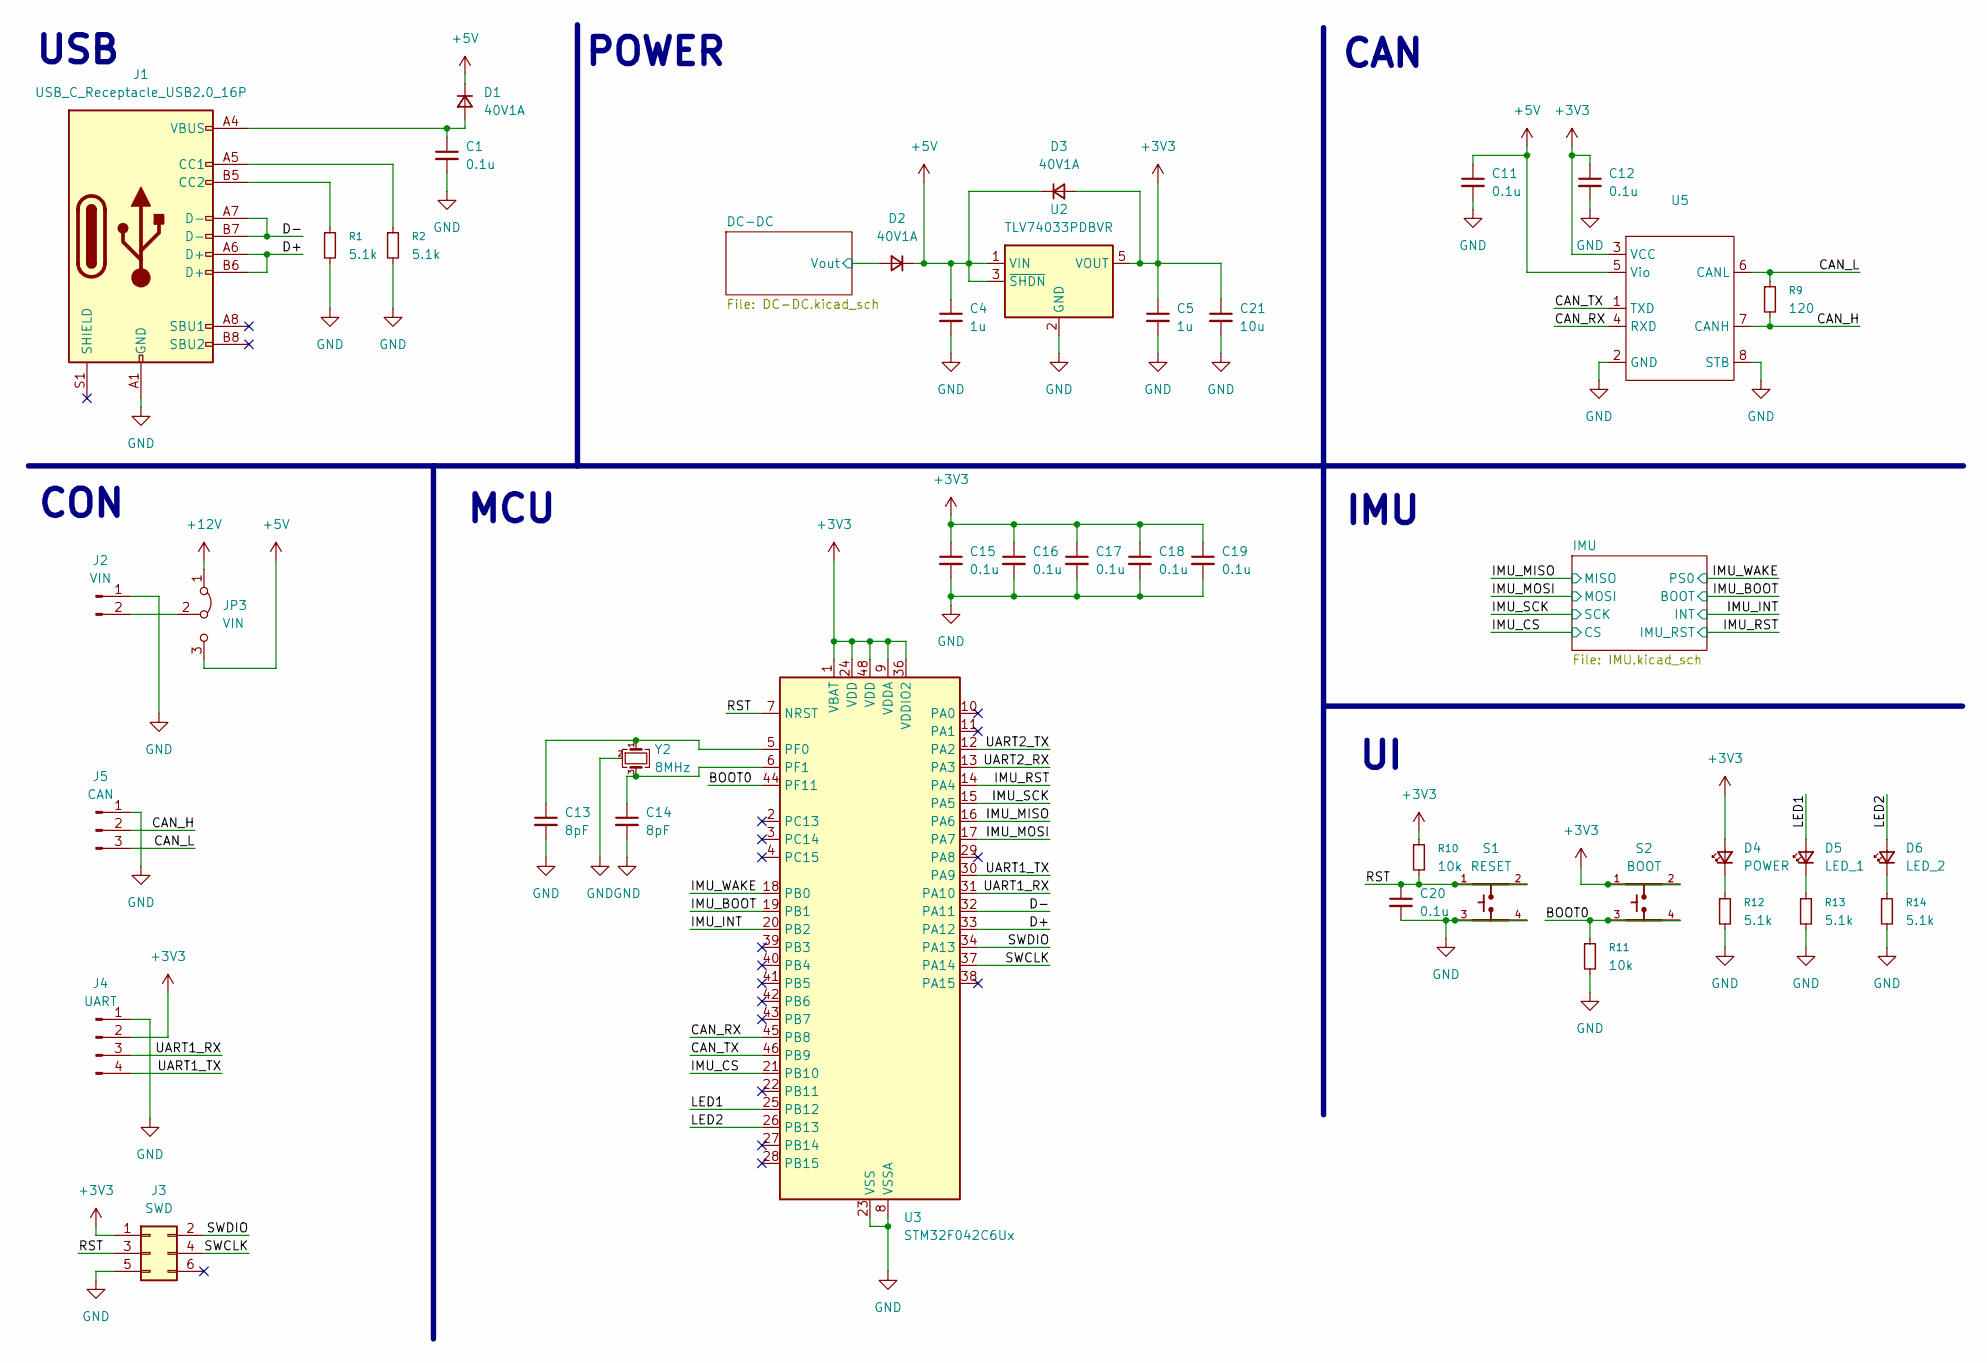
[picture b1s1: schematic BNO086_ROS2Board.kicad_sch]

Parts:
C1, C11, C12, C15, C16, C17, C18, C19, C20: 0.1u; C_0402_1005Metric
C4, C5: 1u; C_0402_1005Metric
C13, C14: 8pF; C_0402_1005Metric
C21: 10u; C_0603_1608Metric
D1, D2, D3: 40V1A; D_SOD-123F
D4: POWER; LED_0603_1608Metric
D5: LED_1; LED_0603_1608Metric
D6: LED_2; LED_0603_1608Metric
J1: USB_C_Receptacle_USB2.0_16P; USB_C_Receptacle_HCTL_HC-TYPE-C-16P-01A
J2: VIN; JST_SH_BM02B-SRSS-TB_1x02-1MP_P1.00mm_Vertical
J3: SWD; PinHeader_2x03_P1.00mm_Vertical
J4: UART; JST_SH_BM04B-SRSS-TB_1x04-1MP_P1.00mm_Vertical
J5: CAN; JST_SH_BM03B-SRSS-TB_1x03-1MP_P1.00mm_Vertical
JP3: VIN; SolderJumper-3_P1.3mm_Bridged12_Pad1.0x1.5mm
R1, R2, R12, R13, R14: 5.1k; R_0402_1005Metric
R9: 120; R_0402_1005Metric
R10, R11: 10k; R_0402_1005Metric
S1: RESET; SW_SKRPACE010
S2: BOOT; SW_SKRPACE010
U2: TLV74033PDBVR; SOT-23-5
U3: STM32F042C6Ux; QFN-48-1EP_7x7mm_P0.5mm_EP5.6x5.6mm
U5: SOT-23-8
Y2: 8MHz; Crystal_SMD_3225-4Pin_3.2x2.5mm

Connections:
+3V3: C5.1, C12.1, C15.1, C16.1, C17.1, C18.1, C19.1, C21.1, D3.2 (A), D4.2 (A), J3.1, J4.2, R10.1, S2.1, S2.2, U2.5 (VOUT), U3.1 (VBAT), U3.9 (VDDA), U3.24 (VDD), U3.36 (VDDIO2), U3.48 (VDD), U5.3 (VCC); also elsewhere on the board
+5V: C4.1, C11.1, D1.1 (K), D2.1 (K), D3.1 (K), JP3.3 (B), U2.1 (VIN), U2.3 (~SHDN), U5.5 (Vio)
+12V: JP3.1 (A); also elsewhere on the board
/BOOT0: R11.1, S2.3, S2.4, U3.44 (PF11)
/CAN_H: J5.2, R9.2, U5.7 (CANH)
/CAN_L: J5.3, R9.1, U5.6 (CANL)
/CAN_RX: U3.45 (PB8), U5.4 (RXD)
/CAN_TX: U3.46 (PB9), U5.1 (TXD)
/D+: J1.A6 (D+), J1.B6 (D+), U3.33 (PA12)
/D-: J1.A7 (D-), J1.B7 (D-), U3.32 (PA11)
/DC-DC/Vout: D2.2 (A); also elsewhere on the board
/IMU_BOOT: U3.19 (PB1); also elsewhere on the board
/IMU_CS: U3.21 (PB10); also elsewhere on the board
/IMU_INT: U3.20 (PB2); also elsewhere on the board
/IMU_MISO: U3.16 (PA6); also elsewhere on the board
/IMU_MOSI: U3.17 (PA7); also elsewhere on the board
/IMU_RST: U3.14 (PA4); also elsewhere on the board
/IMU_SCK: U3.15 (PA5); also elsewhere on the board
/IMU_WAKE: U3.18 (PB0); also elsewhere on the board
/LED1: D5.2 (A), U3.25 (PB12)
/LED2: D6.2 (A), U3.26 (PB13)
/RST: C20.1, J3.3, R10.2, S1.1, S1.2, U3.7 (NRST)
/SWCLK: J3.4, U3.37 (PA14)
/SWDIO: J3.2, U3.34 (PA13)
/UART1_RX: J4.3, U3.31 (PA10)
/UART1_TX: J4.4, U3.30 (PA9)
/UART2_RX: U3.13 (PA3)
/UART2_TX: U3.12 (PA2)
GND: C1.2, C4.2, C5.2, C11.2, C12.2, C13.2, C14.2, C15.2, C16.2, C17.2, C18.2, C19.2, C20.2, C21.2, J1.A1 (GND), J1.A12 (GND), J1.B1 (GND), J1.B12 (GND), J2.1, J3.5, J4.1, J5.1, R1.2, R2.2, R11.2, R12.2, R13.2, R14.2, S1.3, S1.4, U2.2 (GND), U3.8 (VSSA), U3.23 (VSS), U3.35 (VSS), U3.47 (VSS), U3.49 (VSS), U5.2 (GND), U5.8 (STB), Y2.2 (G), Y2.4 (G); also elsewhere on the board
unnamed: C1.1, D1.2 (A), J1.A4 (VBUS), J1.A9 (VBUS), J1.B4 (VBUS), J1.B9 (VBUS)
unnamed: D4.1 (K), R12.1
unnamed: D5.1 (K), R13.1
unnamed: D6.1 (K), R14.1
unnamed: J1.A5 (CC1), R2.1
unnamed: J1.B5 (CC2), R1.1
unnamed: J2.2, JP3.2 (C)
unnamed: C13.1, U3.5 (PF0), Y2.1
unnamed: C14.1, U3.6 (PF1), Y2.3

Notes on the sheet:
IMU
CAN
POWER
USB
CON
MCU

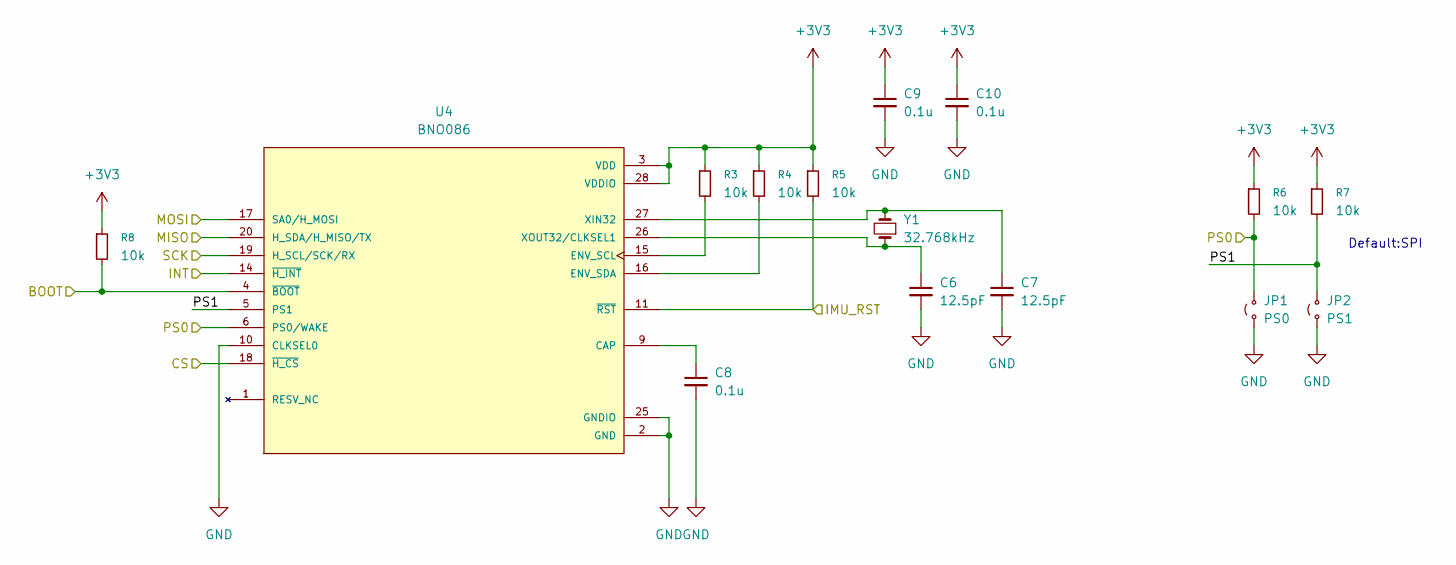
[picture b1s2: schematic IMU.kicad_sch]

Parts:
C6, C7: 12.5pF; C_0402_1005Metric
C8, C9, C10: 0.1u; C_0402_1005Metric
JP1: PS0; SolderJumper-2_P1.3mm_Open_Pad1.0x1.5mm
JP2: PS1; SolderJumper-2_P1.3mm_Open_Pad1.0x1.5mm
R3, R4, R5, R6, R7, R8: 10k; R_0402_1005Metric
U4: BNO086; IC_BNO086; PARTREV v1.17
Y1: 32.768kHz; Crystal_SMD_3215-2Pin_3.2x1.5mm

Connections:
+3V3: C9.1, C10.1, R3.1, R4.1, R5.1, R6.1, R7.1, R8.1, U4.3 (VDD), U4.28 (VDDIO); also elsewhere on the board
/IMU/PS1: JP2.2 (B), R7.2, U4.5 (PS1)
/IMU_BOOT: R8.2, U4.4 (~BOOT); also elsewhere on the board
/IMU_CS: U4.18 (~H_CS); also elsewhere on the board
/IMU_INT: U4.14 (~H_INT); also elsewhere on the board
/IMU_MISO: U4.20 (H_SDA/H_MISO/TX); also elsewhere on the board
/IMU_MOSI: U4.17 (SA0/H_MOSI); also elsewhere on the board
/IMU_RST: R5.2, U4.11 (~RST); also elsewhere on the board
/IMU_SCK: U4.19 (H_SCL/SCK/RX); also elsewhere on the board
/IMU_WAKE: JP1.2 (B), R6.2, U4.6 (PS0/WAKE); also elsewhere on the board
GND: C6.2, C7.2, C8.2, C9.2, C10.2, JP1.1 (A), JP2.1 (A), U4.2 (GND), U4.10 (CLKSEL0), U4.25 (GNDIO); also elsewhere on the board
unnamed: C8.1, U4.9 (CAP)
unnamed: R3.2, U4.15 (ENV_SCL)
unnamed: R4.2, U4.16 (ENV_SDA)
unnamed: C7.1, U4.27 (XIN32), Y1.2
unnamed: C6.1, U4.26 (XOUT32/CLKSEL1), Y1.1

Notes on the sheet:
Default:SPI

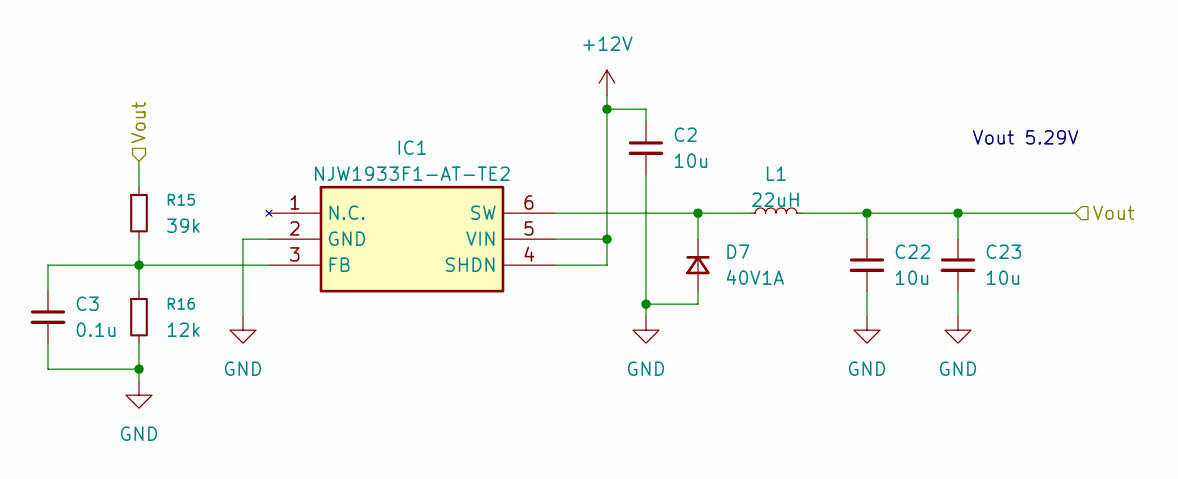
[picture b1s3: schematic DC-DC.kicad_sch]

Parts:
C2, C22, C23: 10u; C_0603_1608Metric
C3: 0.1u; C_0402_1005Metric
D7: 40V1A; D_SOD-123F
IC1: NJW1933F1-AT-TE2; SOT95P280X130-6N; Mouser Part Number 513-NJW1933F1-AT-TE2
L1: 22uH; L_Taiyo-Yuden_MD-4040
R15: 39k; R_0402_1005Metric
R16: 12k; R_0402_1005Metric

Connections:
+12V: C2.1, IC1.4 (SHDN), IC1.5 (VIN); also elsewhere on the board
/DC-DC/Vout: C22.1, C23.1, L1.2, R15.1; also elsewhere on the board
GND: C2.2, C3.2, C22.2, C23.2, D7.2 (A), IC1.2 (GND), R16.2; also elsewhere on the board
unnamed: D7.1 (K), IC1.6 (SW), L1.1
unnamed: C3.1, IC1.3 (FB), R15.2, R16.1

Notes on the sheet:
Vout 5.29V

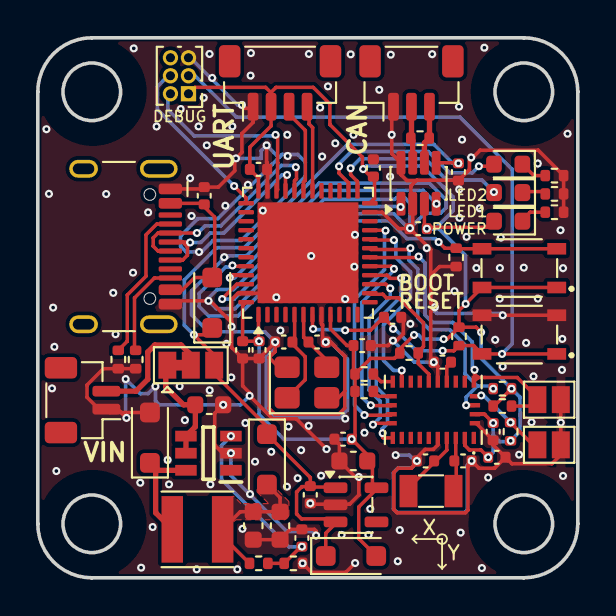
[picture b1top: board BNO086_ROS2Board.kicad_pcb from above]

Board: 2 copper layers, 30.0 x 30.0 mm, 64 parts (0 on the bottom side), 44 nets.

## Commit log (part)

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2026-03-19 add gitignore
2026-04-04 make Docker files
2026-04-04 add epos4 package syboliclink and README
2026-04-08 replace maxon_epos4_ros2 submodule with epos4compact50-5can
2026-04-08 update Dockerfile and docker-compose.yml for CANopen support; fix README typos and add COLCON_IGNORE
2026-04-08 update epos4compact50-5can submodule to latest commit
2026-04-10 add epos4_vel_ros2 package with CMakeLists and source files; update epos4compact50-5can submodule
2026-04-11 add Epos4 control node for dual motor velocity management
2026-04-12 refactor Epos4 control node for dual motor management; enhance input handling and update service calls
2026-04-13 add control_vel_2chanel executable and update dependencies for dual motor control
2026-04-14 add unit tests for epos4 velocity control and update CMakeLists for new executables
2026-04-15 add epos4_controller and epos4_vel_ros2 packages; implement dual motor control node and update CMakeLists
2026-04-15 refactor Epos4 control node; remove input handling thread and related methods for cleaner shutdown process
2026-04-16 refactor epos4_controller; update package name, add geometry_msgs dependency, and implement YAML parameters for tread width and tire diameter
2026-04-19 add epos4_odmetry.cpp; implement odometry functionality for Epos4 control
2026-04-20 add epos4_odmetry; implement odometry node and update CMakeLists and package.xml for dependencies
    start use claude
2026-04-22 add epos4_odometry; implement odometry node and update launch configuration add urdf
2026-04-22 refactor epos4 parameters; add gear_ratio and invert parameters to YAML and update odometry calculations
2026-04-22 add epos4_teleop; implement keyboard teleoperation functionality and update parameters
2026-04-22 add visualization dependencies; include rviz2, rqt, and rqt-common-plugins in Dockerfile
2026-04-26 add rviz2 configuration; include rviz2 auto-start in launch file and add rviz settings
2026-04-28 add message_filters dependency; update CMakeLists.txt and package.xml, refactor odometry to use message_filters for joint state synchronization
2026-05-03 add HOKUYO urg_node and slam toolbox to Dockerfile; update URDF to include laser frame and joint
2026-05-04 update README with hardware setup instructions; modify params.yaml for motor inversion; adjust URDF for laser frame naming; comment out unused robot_state_publisher node in launch file
2026-05-04 refactor: reorganize bringup package structure; move launch, config, URDF, and RViz assets to rerobot_bringup package
2026-05-05 Can display particle data and odometry data in rviz
2026-05-05 feat: add slam_toolbox configuration and launch files; include urg_node dependency in package.xml
2026-05-27 feat: add debug report skill and template; enhance slam_toolbox configuration for message filtering
2026-06-05 feat: add SDO read functionality and improve motor initialization sequence; ensure sequential service calls to prevent race conditions
2026-06-05 feat: implement motor free mode toggle; add subscription and publishing for free mode state
2026-06-07 feat: update motor wiring logic and gear ratio parameters; ensure correct mapping of motor indices to physical wheels
    fix rl motor inversed and gear ratio mismatch
2026-06-08 feat: update Dockerfile and docker-compose.yml; add navigation2 and robot localization packages, and include maps volume
2026-06-11 feat: add Nav2 minimal configuration; include necessary dependencies and launch files for map playback and localization Non checked
2026-06-12 Applicate clang-format - Updated nav2_params.yaml to include keepout filter and costmap filter info server. - Modified nav2.launch.py to support new keepout mask and costmap filter functionalities. -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
2026-06-13 Add debug reports for rfans_driver issues and improve performance
    - Created a report detailing the issue with R-Fans-16 where the device model was not matching (dataID 0x37), resulting in a 2D point cloud with all points at z=0. The root cause was identified as the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
    - Added a report addressing the low point cloud update frequency (approximately 1-2 Hz) in RViz. The issue was traced back to the unnecessary invocation of `rclcpp::spin_some()` within the point proc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
2026-06-13 add joy coctroller settings
2026-06-14 feat: enhance RViz configurations for Nav2 and SLAM; add dedicated views and update launch files to avoid duplicate windows
2026-06-16 feat: implement 2D and 3D LiDAR configurations; add launch files and parameters for epos4_controller and epos4_odometry

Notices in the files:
ros2_ws_main/src/drivers/BNO086_ROS2Board-main/README.md:
License: MIT
